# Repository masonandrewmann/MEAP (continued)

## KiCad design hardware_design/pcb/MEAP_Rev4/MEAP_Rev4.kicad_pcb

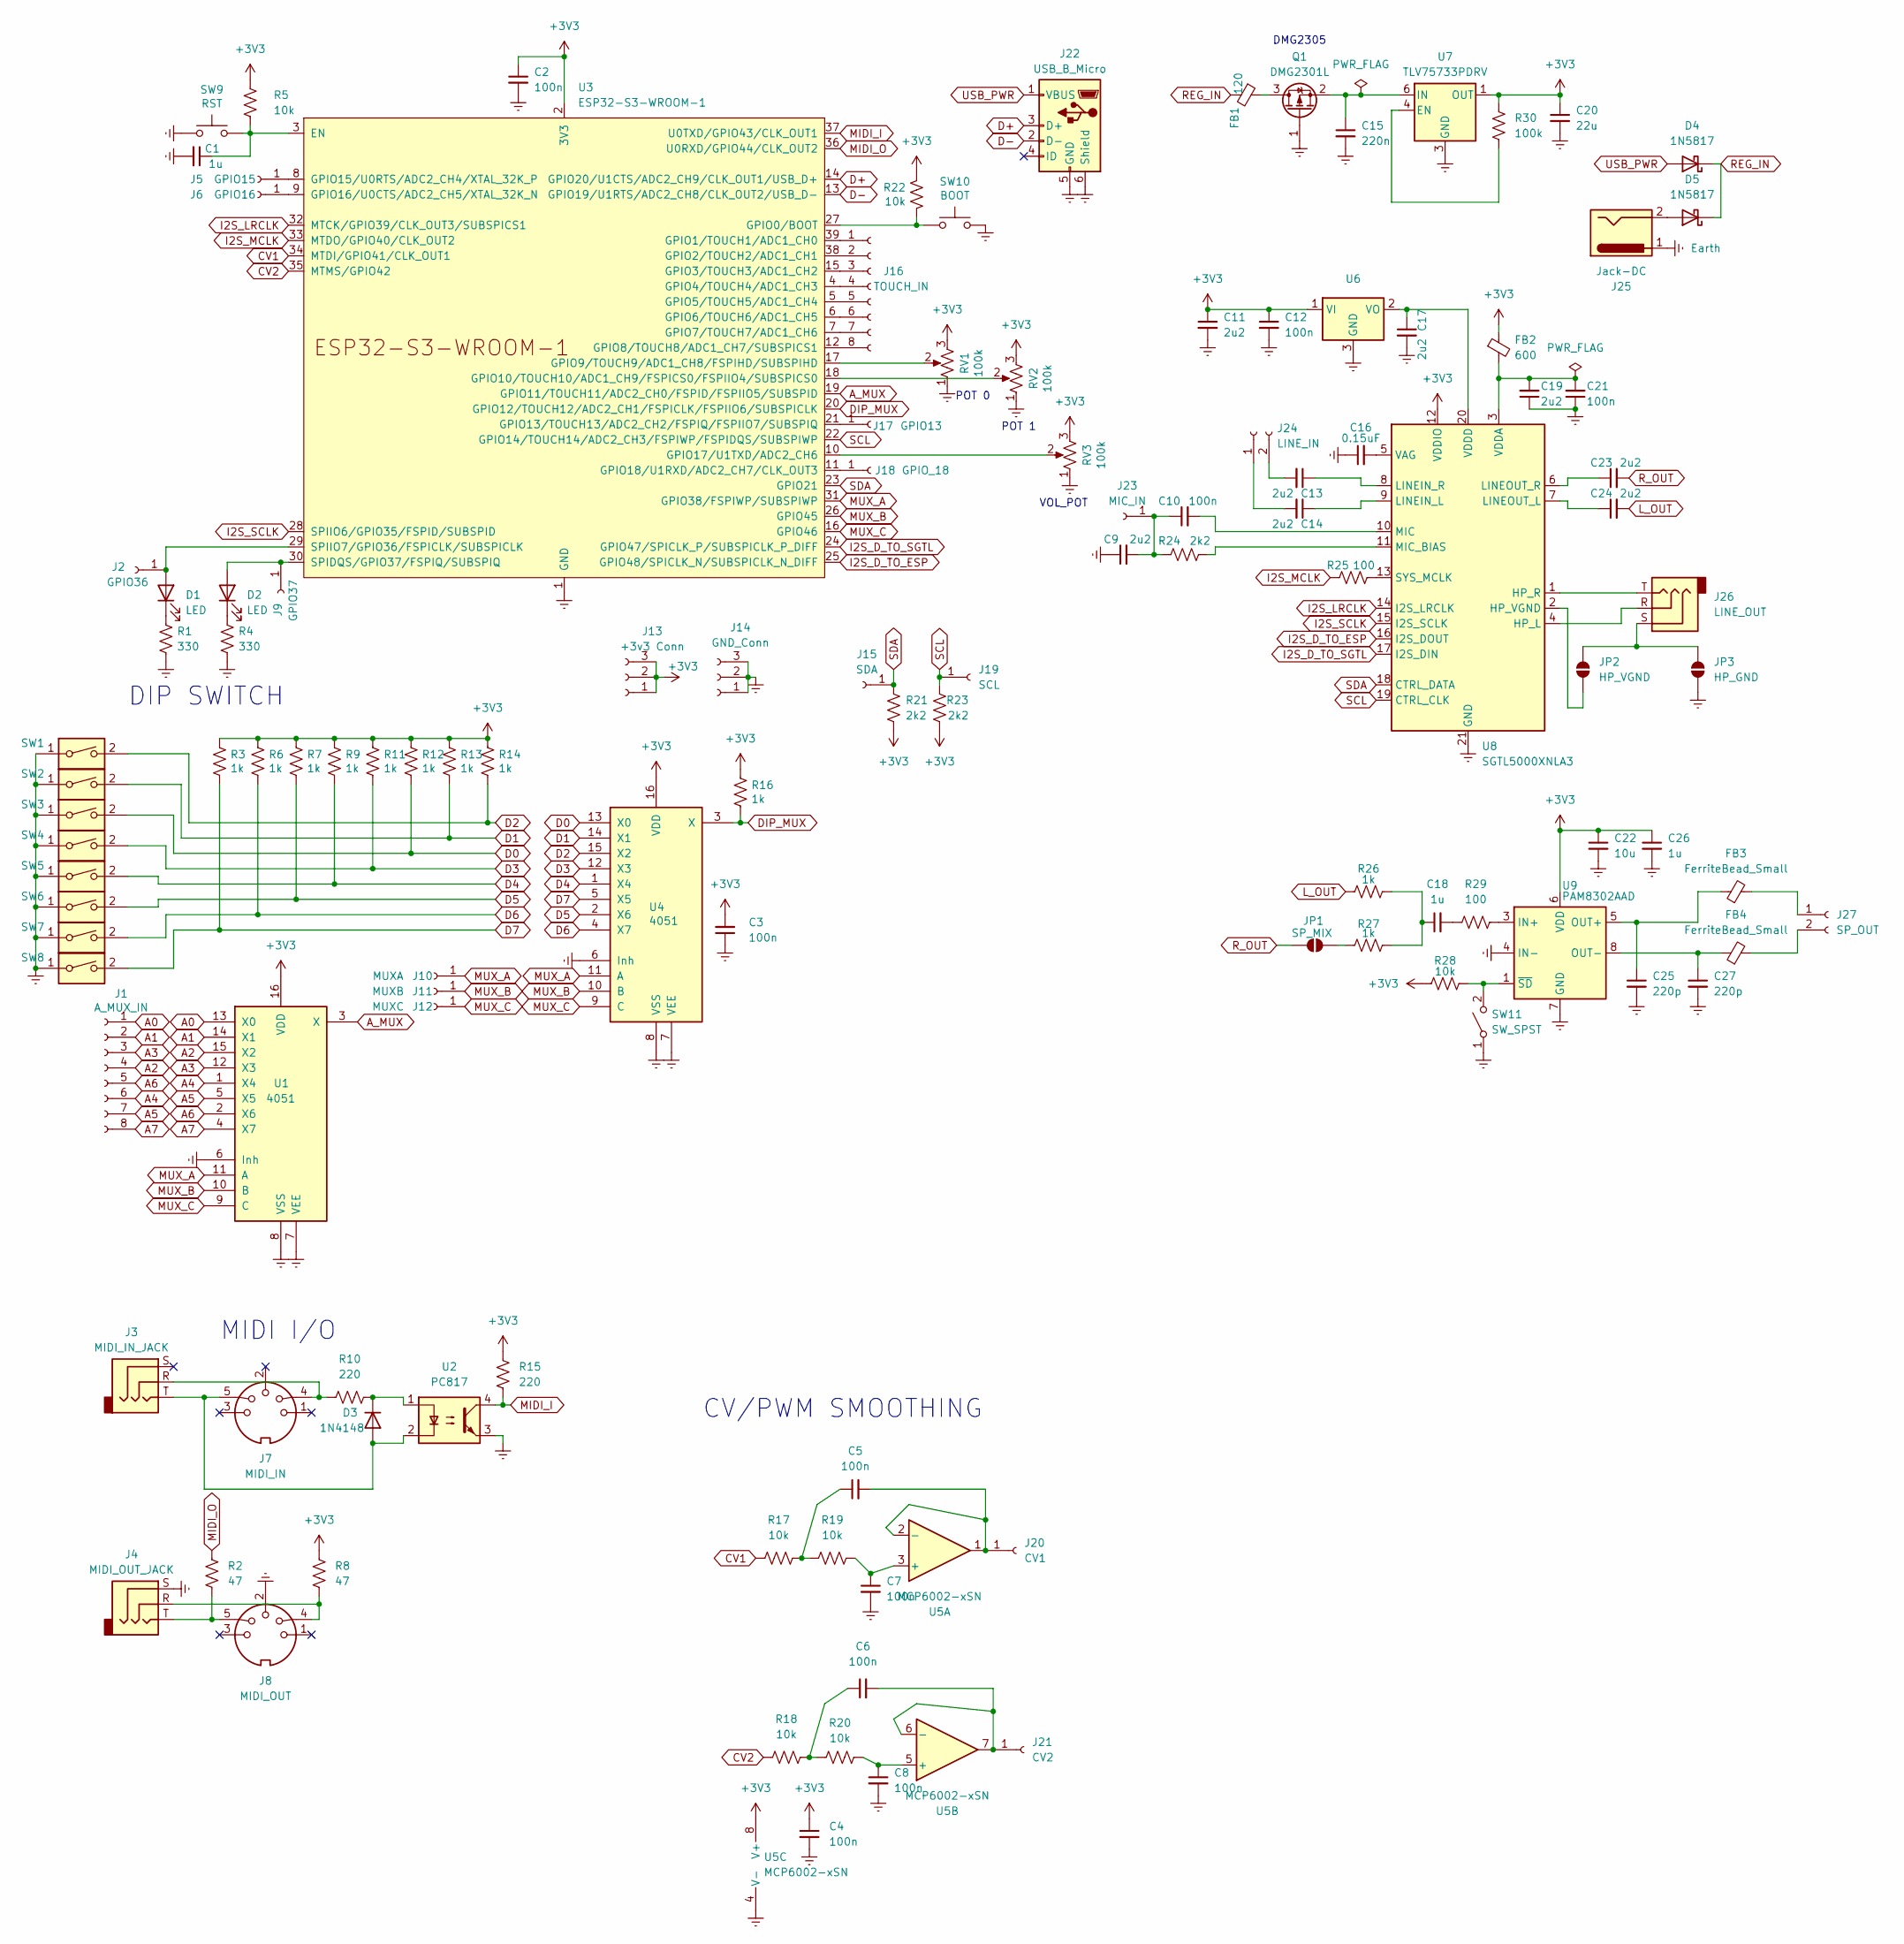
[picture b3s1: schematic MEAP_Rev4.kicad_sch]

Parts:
C1, C18, C26: 1u; C_0603_1608Metric_Pad1.08x0.95mm_HandSolder
C2, C3, C4, C5, C6, C7, C8, C10, C12, C21: 100n; C_0603_1608Metric_Pad1.08x0.95mm_HandSolder
C9, C11, C13, C14, C17, C19, C23, C24: 2u2; C_0603_1608Metric_Pad1.08x0.95mm_HandSolder
C15: 220n; C_0603_1608Metric_Pad1.08x0.95mm_HandSolder
C16: 0.15uF; C_0603_1608Metric_Pad1.08x0.95mm_HandSolder
C20: 22u; C_1210_3225Metric
C22: 10u; C_0603_1608Metric_Pad1.08x0.95mm_HandSolder
C25, C27: 220p; C_0603_1608Metric_Pad1.08x0.95mm_HandSolder
D1, D2: LED; LED_D3.0mm_Clear
D3: 1N4148; D_SOD-323
D4, D5: 1N5817; D_DO-41_SOD81_P2.54mm_Vertical_KathodeUp
FB1: 120; L_0603_1608Metric
FB2: 600; L_0603_1608Metric
FB3, FB4: FerriteBead_Small; L_0603_1608Metric
J1: A_MUX_IN; PinHeader_2x04_P2.54mm_Vertical
J2: GPIO36; Pin_D1.0mm_L10.0mm
J3: MIDI_IN_JACK; Jack_3.5mm_CUI_SJ1-3535NG_Horizontal_NO_FRONT
J4: MIDI_OUT_JACK; Jack_3.5mm_CUI_SJ1-3535NG_Horizontal_NO_FRONT
J5: GPIO15; Pin_D1.0mm_L10.0mm
J6: GPIO16; Pin_D1.0mm_L10.0mm
J7: MIDI_IN
J8: MIDI_OUT
J9: GPIO37; Pin_D1.0mm_L10.0mm
J10: MUXA; Pin_D1.0mm_L10.0mm
J11: MUXB; Pin_D1.0mm_L10.0mm
J12: MUXC; Pin_D1.0mm_L10.0mm
J13: +3v3 Conn; PinHeader_1x03_P2.54mm_Vertical
J14: GND_Conn; PinHeader_1x03_P2.54mm_Vertical
J15: SDA; Pin_D1.0mm_L10.0mm
J16: TOUCH_IN; PinHeader_2x04_P2.54mm_Vertical
J17: GPIO13; Pin_D1.0mm_L10.0mm
J18: GPIO_18; Pin_D1.0mm_L10.0mm
J19: SCL; Pin_D1.0mm_L10.0mm
J20: CV1; Pin_D1.0mm_L10.0mm
J21: CV2; Pin_D1.0mm_L10.0mm
J22: USB_B_Micro; USB_Micro-B_Molex-105017-0001
J23: MIC_IN; Pin_D1.0mm_L10.0mm
J24: LINE_IN; PinHeader_1x02_P2.54mm_Vertical
J25: Jack-DC; BarrelJack_Horizontal
J26: LINE_OUT; Jack_3.5mm_CUI_SJ1-3535NG_Horizontal_NO_FRONT
J27: SP_OUT; PinHeader_1x02_P2.54mm_Vertical
JP1: SP_MIX; SolderJumper-2_P1.3mm_Open_Pad1.0x1.5mm
JP2: HP_VGND; SolderJumper-2_P1.3mm_Open_RoundedPad1.0x1.5mm
JP3: HP_GND; SolderJumper-2_P1.3mm_Open_RoundedPad1.0x1.5mm
Q1: DMG2301L; SOT-23
R1, R4: 330; R_0603_1608Metric_Pad0.98x0.95mm_HandSolder
R2, R8: 47; R_0603_1608Metric_Pad0.98x0.95mm_HandSolder
R3, R6, R7, R9, R11, R12, R13, R14, R16, R26, R27: 1k; R_0603_1608Metric_Pad0.98x0.95mm_HandSolder
R5, R17, R18, R19, R20, R22, R28: 10k; R_0603_1608Metric_Pad0.98x0.95mm_HandSolder
R10, R15: 220; R_0603_1608Metric_Pad0.98x0.95mm_HandSolder
R21, R23, R24: 2k2; R_0603_1608Metric_Pad0.98x0.95mm_HandSolder
R25, R29: 100; R_0603_1608Metric_Pad0.98x0.95mm_HandSolder
R30: 100k; R_0603_1608Metric_Pad0.98x0.95mm_HandSolder
RV1, RV2, RV3: 100k; PinHeader_1x03_P2.54mm_Vertical
SW1, SW2, SW3, SW4, SW5, SW6, SW7, SW8: SW_DIP_x01; SINGLE_DIP_SWITCH
SW9: RST; SW_Tactile_SPST_NO_Straight_CK_PTS636Sx25SMTRLFS
SW10: BOOT; SW_Tactile_SPST_NO_Straight_CK_PTS636Sx25SMTRLFS
SW11: SW_SPST; SW_Slide_SPDT_Straight_CK_OS102011MS2Q
U1, U4: 4051; SOIC-16_3.9x9.9mm_P1.27mm
U2: PC817; DIP-4_W7.62mm
U3: ESP32-S3-WROOM-1; ESP32-S3-WROOM-1U
U5: MCP6002-xSN; SOIC-8_3.9x4.9mm_P1.27mm
U6: SOT-23
U7: TLV75733PDRV; WSON-6-1EP_2x2mm_P0.65mm_EP1x1.6mm
U8: SGTL5000XNLA3; QFN-20-1EP_3x3mm_P0.4mm_EP1.65x1.65mm
U9: PAM8302AAD; MSOP-8_3x3mm_P0.65mm

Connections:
+3V3: C2.1, C3.2, C4.1, C11.1, C12.1, C20.1, C22.1, C26.1, FB2.1, J13.1, J13.2, J13.3, R3.1, R5.1, R6.1, R7.1, R8.1, R9.1, R11.1, R12.1, R13.1, R14.1, R15.1, R16.1, R21.2, R22.1, R23.2, R28.1, R30.1, RV1.3, RV2.3, RV3.3, U1.16 (VDD), U3.2 (3V3), U4.16 (VDD), U5.8 (V+), U6.1 (VI), U7.1 (OUT), U8.12 (VDDIO), U9.6 (VDD)
A0: J1.1, U1.13 (X0)
A1: J1.2, U1.14 (X1)
A2: J1.4, U1.15 (X2)
A3: J1.3, U1.12 (X3)
A4: J1.6, U1.1 (X4)
A5: J1.7, U1.5 (X5)
A6: J1.5, U1.2 (X6)
A7: J1.8, U1.4 (X7)
A_MUX: U1.3 (X), U3.19 (GPIO11/TOUCH11/ADC2_CH0/FSPID/FSPIIO5/S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)
CV1: R17.1, U3.34 (MTDI/GPIO41/CLK_OUT1)
CV2: R18.1, U3.35 (MTMS/GPIO42)
D0: R12.2, SW3.2, U4.13 (X0)
D1: R13.2, SW2.2, U4.14 (X1)
D2: R14.2, SW1.2, U4.15 (X2)
D3: R11.2, SW4.2, U4.12 (X3)
D4: R9.2, SW5.2, U4.1 (X4)
D5: R7.2, SW6.2, U4.2 (X6)
D6: R6.2, SW7.2, U4.4 (X7)
D7: R3.2, SW8.2, U4.5 (X5)
D+: J22.3 (D+), U3.14 (GPIO20/U1CTS/ADC2_CH9/CLK_OUT1/USB_D+)
D-: J22.2 (D-), U3.13 (GPIO19/U1RTS/ADC2_CH8/CLK_OUT2/USB_D-)
DIP_MUX: R16.2, U3.20 (GPIO12/TOUCH12/ADC2_CH1/FSPICLK/FSPIIO6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), U4.3 (X)
Earth: C1.2, C2.2, C3.1, C4.2, C7.2, C8.2, C9.1, C11.2, C12.2, C15.2, C16.1, C17.2, C19.1, C20.2, C21.1, C22.2, C25.2, C26.2, C27.2, J4.S, J8.2, J14.1, J14.2, J14.3, J22.5 (GND), J22.6 (Shield), J25.1, JP3.1 (A), Q1.1 (G), R1.2, R4.2, RV1.1, RV2.1, RV3.1, SW1.1, SW2.1, SW3.1, SW4.1, SW5.1, SW6.1, SW7.1, SW8.1, SW9.1, SW10.2, SW11.1 (A), U1.6 (Inh), U1.7 (VEE), U1.8 (VSS), U2.3, U3.1 (GND), U3.40 (GND), U3.41 (GND), U4.6 (Inh), U4.7 (VEE), U4.8 (VSS), U5.4 (V-), U6.3 (GND), U7.3 (GND), U7.7 (GND), U8.21 (GND), U9.4 (IN-), U9.7 (GND)
I2S_D_TO_ESP: U3.25 (GPIO48/SPICLK_N/SUBSPICLK_N_DIFF), U8.16 (I2S_DOUT)
I2S_D_TO_SGTL: U3.24 (GPIO47/SPICLK_P/SUBSPICLK_P_DIFF), U8.17 (I2S_DIN)
I2S_LRCLK: U3.32 (MTCK/GPIO39/CLK_OUT3/SUBSPICS1), U8.14 (I2S_LRCLK)
I2S_MCLK: R25.1, U3.33 (MTDO/GPIO40/CLK_OUT2)
I2S_SCLK: U3.28 (SPIIO6/GPIO35/FSPID/SUBSPID), U8.15 (I2S_SCLK)
L_OUT: C24.2, R26.1
MIDI_I: R15.2, U2.4, U3.37 (U0TXD/GPIO43/CLK_OUT1)
MIDI_O: R2.1, U3.36 (U0RXD/GPIO44/CLK_OUT2)
MUX_A: J10.1, U1.11 (A), U3.31 (GPIO38/FSPIWP/SUBSPIWP), U4.11 (A)
MUX_B: J11.1, U1.10 (B), U3.26 (GPIO45), U4.10 (B)
MUX_C: J12.1, U1.9 (C), U3.16 (GPIO46), U4.9 (C)
unnamed: C5.1, R17.2, R19.1
unnamed: C6.1, R18.2, R20.1
unnamed: C18.1, R26.2, R27.2
unnamed: C18.2, R29.1
unnamed: D1.2 (A), J2.1, U3.29 (SPIIO7/GPIO36/FSPICLK/SUBSPICLK)
unnamed: D1.1 (K), R1.1
unnamed: D2.2 (A), J9.1, U3.30 (SPIDQS/GPIO37/FSPIQ/SUBSPIQ)
unnamed: D2.1 (K), R4.1
unnamed: D3.2 (A), J3.T, J7.5, U2.2
unnamed: D3.1 (K), R10.2, U2.1
unnamed: D5.2 (A), J25.2
unnamed: J3.R, J7.4, R10.1
unnamed: J4.R, J8.4, R8.2
unnamed: J4.T, J8.5, R2.2
unnamed: J5.1, U3.8 (GPIO15/U0RTS/ADC2_CH4/XTAL_32K_P)
unnamed: J6.1, U3.9 (GPIO16/U0CTS/ADC2_CH5/XTAL_32K_N)
unnamed: J16.1, U3.39 (GPIO1/TOUCH1/ADC1_CH0)
unnamed: J16.2, U3.38 (GPIO2/TOUCH2/ADC1_CH1)
unnamed: J16.3, U3.15 (GPIO3/TOUCH3/ADC1_CH2)
unnamed: J16.4, U3.4 (GPIO4/TOUCH4/ADC1_CH3)
unnamed: J16.5, U3.5 (GPIO5/TOUCH5/ADC1_CH4)
unnamed: J16.6, U3.6 (GPIO6/TOUCH6/ADC1_CH5)
unnamed: J16.7, U3.7 (GPIO7/TOUCH7/ADC1_CH6)
unnamed: J16.8, U3.12 (GPIO8/TOUCH8/ADC1_CH7/SUBSPICS1)
unnamed: J17.1, U3.21 (GPIO13/TOUCH13/ADC2_CH2/FSPIQ/FSPIIO7/S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)
unnamed: J18.1, U3.11 (GPIO18/U1RXD/ADC2_CH7/CLK_OUT3)
unnamed: C5.2, J20.1, U5.1, U5.2 (-)
unnamed: C6.2, J21.1, U5.6 (-), U5.7
unnamed: C9.2, C10.1, J23.1, R24.1
unnamed: C14.2, J24.1
unnamed: C13.2, J24.2
unnamed: FB3.2, J27.1
unnamed: FB4.2, J27.2
unnamed: JP1.1 (A), R27.1
unnamed: JP2.1 (A), U8.2 (HP_VGND)
unnamed: J26.S, JP2.2 (B), JP3.2 (B)
unnamed: FB1.1, Q1.3 (D)
unnamed: C15.1, Q1.2 (S), U7.6 (IN)
unnamed: R28.2, SW11.2 (B), U9.1 (~SD)
unnamed: C1.1, R5.2, SW9.2, U3.3 (EN)
unnamed: R22.2, SW10.1, U3.27 (GPIO0/BOOT)
unnamed: RV1.2, U3.17 (GPIO9/TOUCH9/ADC1_CH8/FSPIHD/SUBSPIHD)
unnamed: RV2.2, U3.18 (GPIO10/TOUCH10/ADC1_CH9/FSPICS0/FSPIIO4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)
unnamed: RV3.2, U3.10 (GPIO17/U1TXD/ADC2_CH6)
unnamed: C7.1, R19.2, U5.3 (+)
unnamed: C8.1, R20.2, U5.5 (+)
unnamed: C17.1, U6.2 (VO), U8.20 (VDDD)
unnamed: R30.2, U7.4 (EN)
unnamed: J26.R, U8.4 (HP_L)
unnamed: J26.T, U8.1 (HP_R)
unnamed: C14.1, U8.9 (LINEIN_L)
unnamed: C13.1, U8.8 (LINEIN_R)
unnamed: C24.1, U8.7 (LINEOUT_L)
unnamed: C23.1, U8.6 (LINEOUT_R)
unnamed: C10.2, U8.10 (MIC)
unnamed: R24.2, U8.11 (MIC_BIAS)
unnamed: R25.2, U8.13 (SYS_MCLK)
unnamed: C16.2, U8.5 (VAG)
unnamed: C19.2, C21.2, FB2.2, U8.3 (VDDA)
unnamed: R29.2, U9.3 (IN+)
unnamed: C25.1, FB3.1, U9.5 (OUT+)
unnamed: C27.1, FB4.1, U9.8 (OUT-)
REG_IN: D4.1 (K), D5.1 (K), FB1.2
R_OUT: C23.2, JP1.2 (B)
SCL: J19.1, R23.1, U3.22 (GPIO14/TOUCH14/ADC2_CH3/FSPIWP/FSPIDQS/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), U8.19 (CTRL_CLK)
SDA: J15.1, R21.1, U3.23 (GPIO21), U8.18 (CTRL_DATA)
USB_PWR: D4.2 (A), J22.1 (VBUS)

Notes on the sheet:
CV/PWM SMOOTHING
VOL_POT
POT 1
DMG2305
POT 0
DIP SWITCH
MIDI I/O

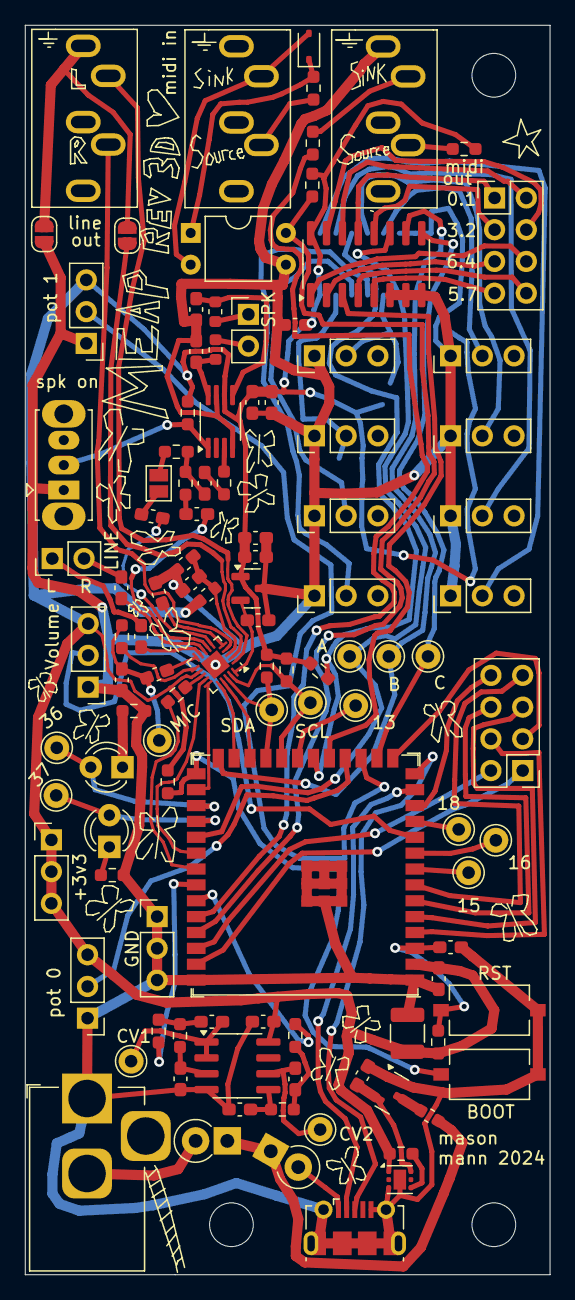
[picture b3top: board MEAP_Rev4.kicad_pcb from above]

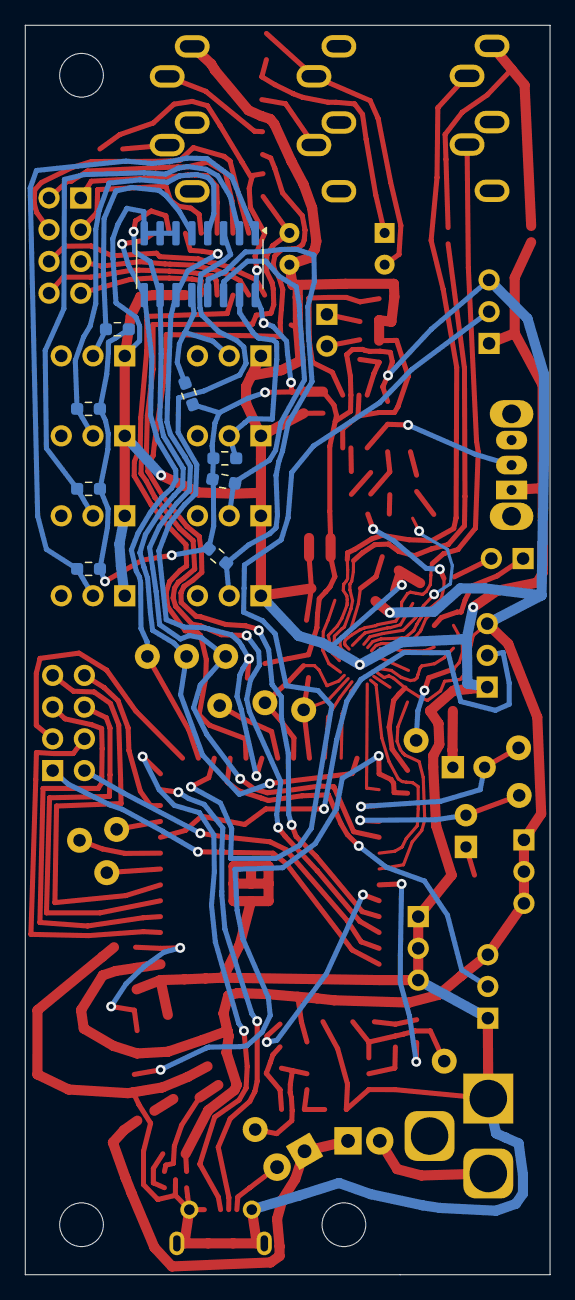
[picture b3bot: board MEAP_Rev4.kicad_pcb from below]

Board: 2 copper layers, 42.0 x 100.0 mm, 118 parts (9 on the bottom side), 102 nets.

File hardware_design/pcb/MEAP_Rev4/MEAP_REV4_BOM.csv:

"Reference","Value","Footprint","Qty","DNP"
"U9","PAM8302AAD","Package_SO:MSOP-8_3x3mm_P0.65mm","1",""
"U8","SGTL5000XNLA3","Package_DFN_QFN:QFN-20-1EP_3x3mm_P0.4mm_EP1.65x1.65mm","1",""
"U7","TLV75733PDRV","Package_SON:WSON-6-1EP_2x2mm_P0.65mm_EP1x1.6mm","1",""
"U6","~","Package_TO_SOT_SMD:SOT-23","1",""
"U5","MCP6002-xSN","Package_SO:SOIC-8_3.9x4.9mm_P1.27mm","1",""
"U3","ESP32-S3-WROOM-1","PCM_Espressif:ESP32-S3-WROOM-1U","1",""
"U2","PC817","Package_DIP:DIP-4_W7.62mm","1",""
"U1,U4","4051","Package_SO:SOIC-16_3.9x9.9mm_P1.27mm","2",""
"SW11","SW_SPST","Button_Switch_THT:SW_Slide_SPDT_Straight_CK_OS102011MS2Q","1",""
"SW10","BOOT","Button_Switch_SMD:SW_Tactile_SPST_NO_Straight_CK_PTS636Sx25SMTRLFS","1",""
"SW9","RST","Button_Switch_SMD:SW_Tactile_SPST_NO_Straight_CK_PTS636Sx25SMTRLFS","1",""
"SW1,SW2,SW3,SW4,SW5,SW6,SW7,SW8","SW_DIP_x01","mason_parts:SINGLE_DIP_SWITCH","8",""
"RV1,RV2,RV3","100k","Connector_PinHeader_2.54mm:PinHeader_1x03_P2.54mm_Vertical","3",""
"R30","100k","Resistor_SMD:R_0603_1608Metric_Pad0.98x0.95mm_HandSolder","1",""
"R25,R29","100","Resistor_SMD:R_0603_1608Metric_Pad0.98x0.95mm_HandSolder","2",""
"R21,R23,R24","2k2","Resistor_SMD:R_0603_1608Metric_Pad0.98x0.95mm_HandSolder","3",""
"R10,R15","220","Resistor_SMD:R_0603_1608Metric_Pad0.98x0.95mm_HandSolder","2",""
"R5,R17,R18,R19,R20,R22,R28","10k","Resistor_SMD:R_0603_1608Metric_Pad0.98x0.95mm_HandSolder","7",""
"R3,R6,R7,R9,R11,R12,R13,R14,R16,R26,R27","1k","Resistor_SMD:R_0603_1608Metric_Pad0.98x0.95mm_HandSolder","11",""
"R2,R8","47","Resistor_SMD:R_0603_1608Metric_Pad0.98x0.95mm_HandSolder","2",""
"R1,R4","330","Resistor_SMD:R_0603_1608Metric_Pad0.98x0.95mm_HandSolder","2",""
"Q1","DMG2301L","Package_TO_SOT_SMD:SOT-23","1",""
"J27","SP_OUT","Connector_PinHeader_2.54mm:PinHeader_1x02_P2.54mm_Vertical","1",""
"J26","LINE_OUT","mason_parts:Jack_3.5mm_CUI_SJ1-3535NG_Horizontal_NO_FRONT","1",""
"J25","Jack-DC","mason_parts:BarrelJack_Horizontal","1",""
"J24","LINE_IN","Connector_PinHeader_2.54mm:PinHeader_1x02_P2.54mm_Vertical","1",""
"J23","MIC_IN","Connector_Pin:Pin_D1.0mm_L10.0mm","1",""
"J22","USB_B_Micro","Connector_USB:USB_Micro-B_Molex-105017-0001","1",""
"J21","CV2","Connector_Pin:Pin_D1.0mm_L10.0mm","1",""
"J20","CV1","Connector_Pin:Pin_D1.0mm_L10.0mm","1",""
"J19","SCL","Connector_Pin:Pin_D1.0mm_L10.0mm","1",""
"J18","GPIO_18","Connector_Pin:Pin_D1.0mm_L10.0mm","1",""
"J17","GPIO13","Connector_Pin:Pin_D1.0mm_L10.0mm","1",""
"J16","TOUCH_IN","Connector_PinHeader_2.54mm:PinHeader_2x04_P2.54mm_Vertical","1",""
"J15","SDA","Connector_Pin:Pin_D1.0mm_L10.0mm","1",""
"J14","GND_Conn","Connector_PinHeader_2.54mm:PinHeader_1x03_P2.54mm_Vertical","1",""
"J13","+3v3 Conn","Connector_PinHeader_2.54mm:PinHeader_1x03_P2.54mm_Vertical","1",""
"J12","MUXC","Connector_Pin:Pin_D1.0mm_L10.0mm","1",""
"J11","MUXB","Connector_Pin:Pin_D1.0mm_L10.0mm","1",""
"J10","MUXA","Connector_Pin:Pin_D1.0mm_L10.0mm","1",""
"J9","GPIO37","Connector_Pin:Pin_D1.0mm_L10.0mm","1",""
"J8","MIDI_OUT","","1",""
"J7","MIDI_IN","","1",""
"J6","GPIO16","Connector_Pin:Pin_D1.0mm_L10.0mm","1",""
"J5","GPIO15","Connector_Pin:Pin_D1.0mm_L10.0mm","1",""
"J4","MIDI_OUT_JACK","mason_parts:Jack_3.5mm_CUI_SJ1-3535NG_Horizontal_NO_FRONT","1",""
"J3","MIDI_IN_JACK","mason_parts:Jack_3.5mm_CUI_SJ1-3535NG_Horizontal_NO_FRONT","1",""
"J2","GPIO36","Connector_Pin:Pin_D1.0mm_L10.0mm","1",""
"J1","A_MUX_IN","Connector_PinHeader_2.54mm:PinHeader_2x04_P2.54mm_Vertical","1",""
"FB3,FB4","FerriteBead_Small","Inductor_SMD:L_0603_1608Metric","2",""
"FB2","600","Inductor_SMD:L_0603_1608Metric","1",""
"FB1","120","Inductor_SMD:L_0603_1608Metric","1",""
"D4,D5","1N5817","Diode_THT:D_DO-41_SOD81_P2.54mm_Vertical_KathodeUp","2",""
"D3","1N4148","Diode_SMD:D_SOD-323","1",""
"D1,D2","LED","LED_THT:LED_D3.0mm_Clear","2",""
"C25,C27","220p","Capacitor_SMD:C_0603_1608Metric_Pad1.08x0.95mm_HandSolder","2",""
"C22","10u","Capacitor_SMD:C_0603_1608Metric_Pad1.08x0.95mm_HandSolder","1",""
"C20","22u","Capacitor_SMD:C_1210_3225Metric","1",""
"C16","0.15uF","Capacitor_SMD:C_0603_1608Metric_Pad1.08x0.95mm_HandSolder","1",""
"C15","220n","Capacitor_SMD:C_0603_1608Metric_Pad1.08x0.95mm_HandSolder","1",""
"C9,C11,C13,C14,C17,C19,C23,C24","2u2","Capacitor_SMD:C_0603_1608Metric_Pad1.08x0.95mm_HandSolder","8",""
"C2,C3,C4,C5,C6,C7,C8,C10,C12,C21","100n","Capacitor_SMD:C_0603_1608Metric_Pad1.08x0.95mm_HandSolder","10",""
"C1,C18,C26","1u","Capacitor_SMD:C_0603_1608Metric_Pad1.08x0.95mm_HandSolder","3",""

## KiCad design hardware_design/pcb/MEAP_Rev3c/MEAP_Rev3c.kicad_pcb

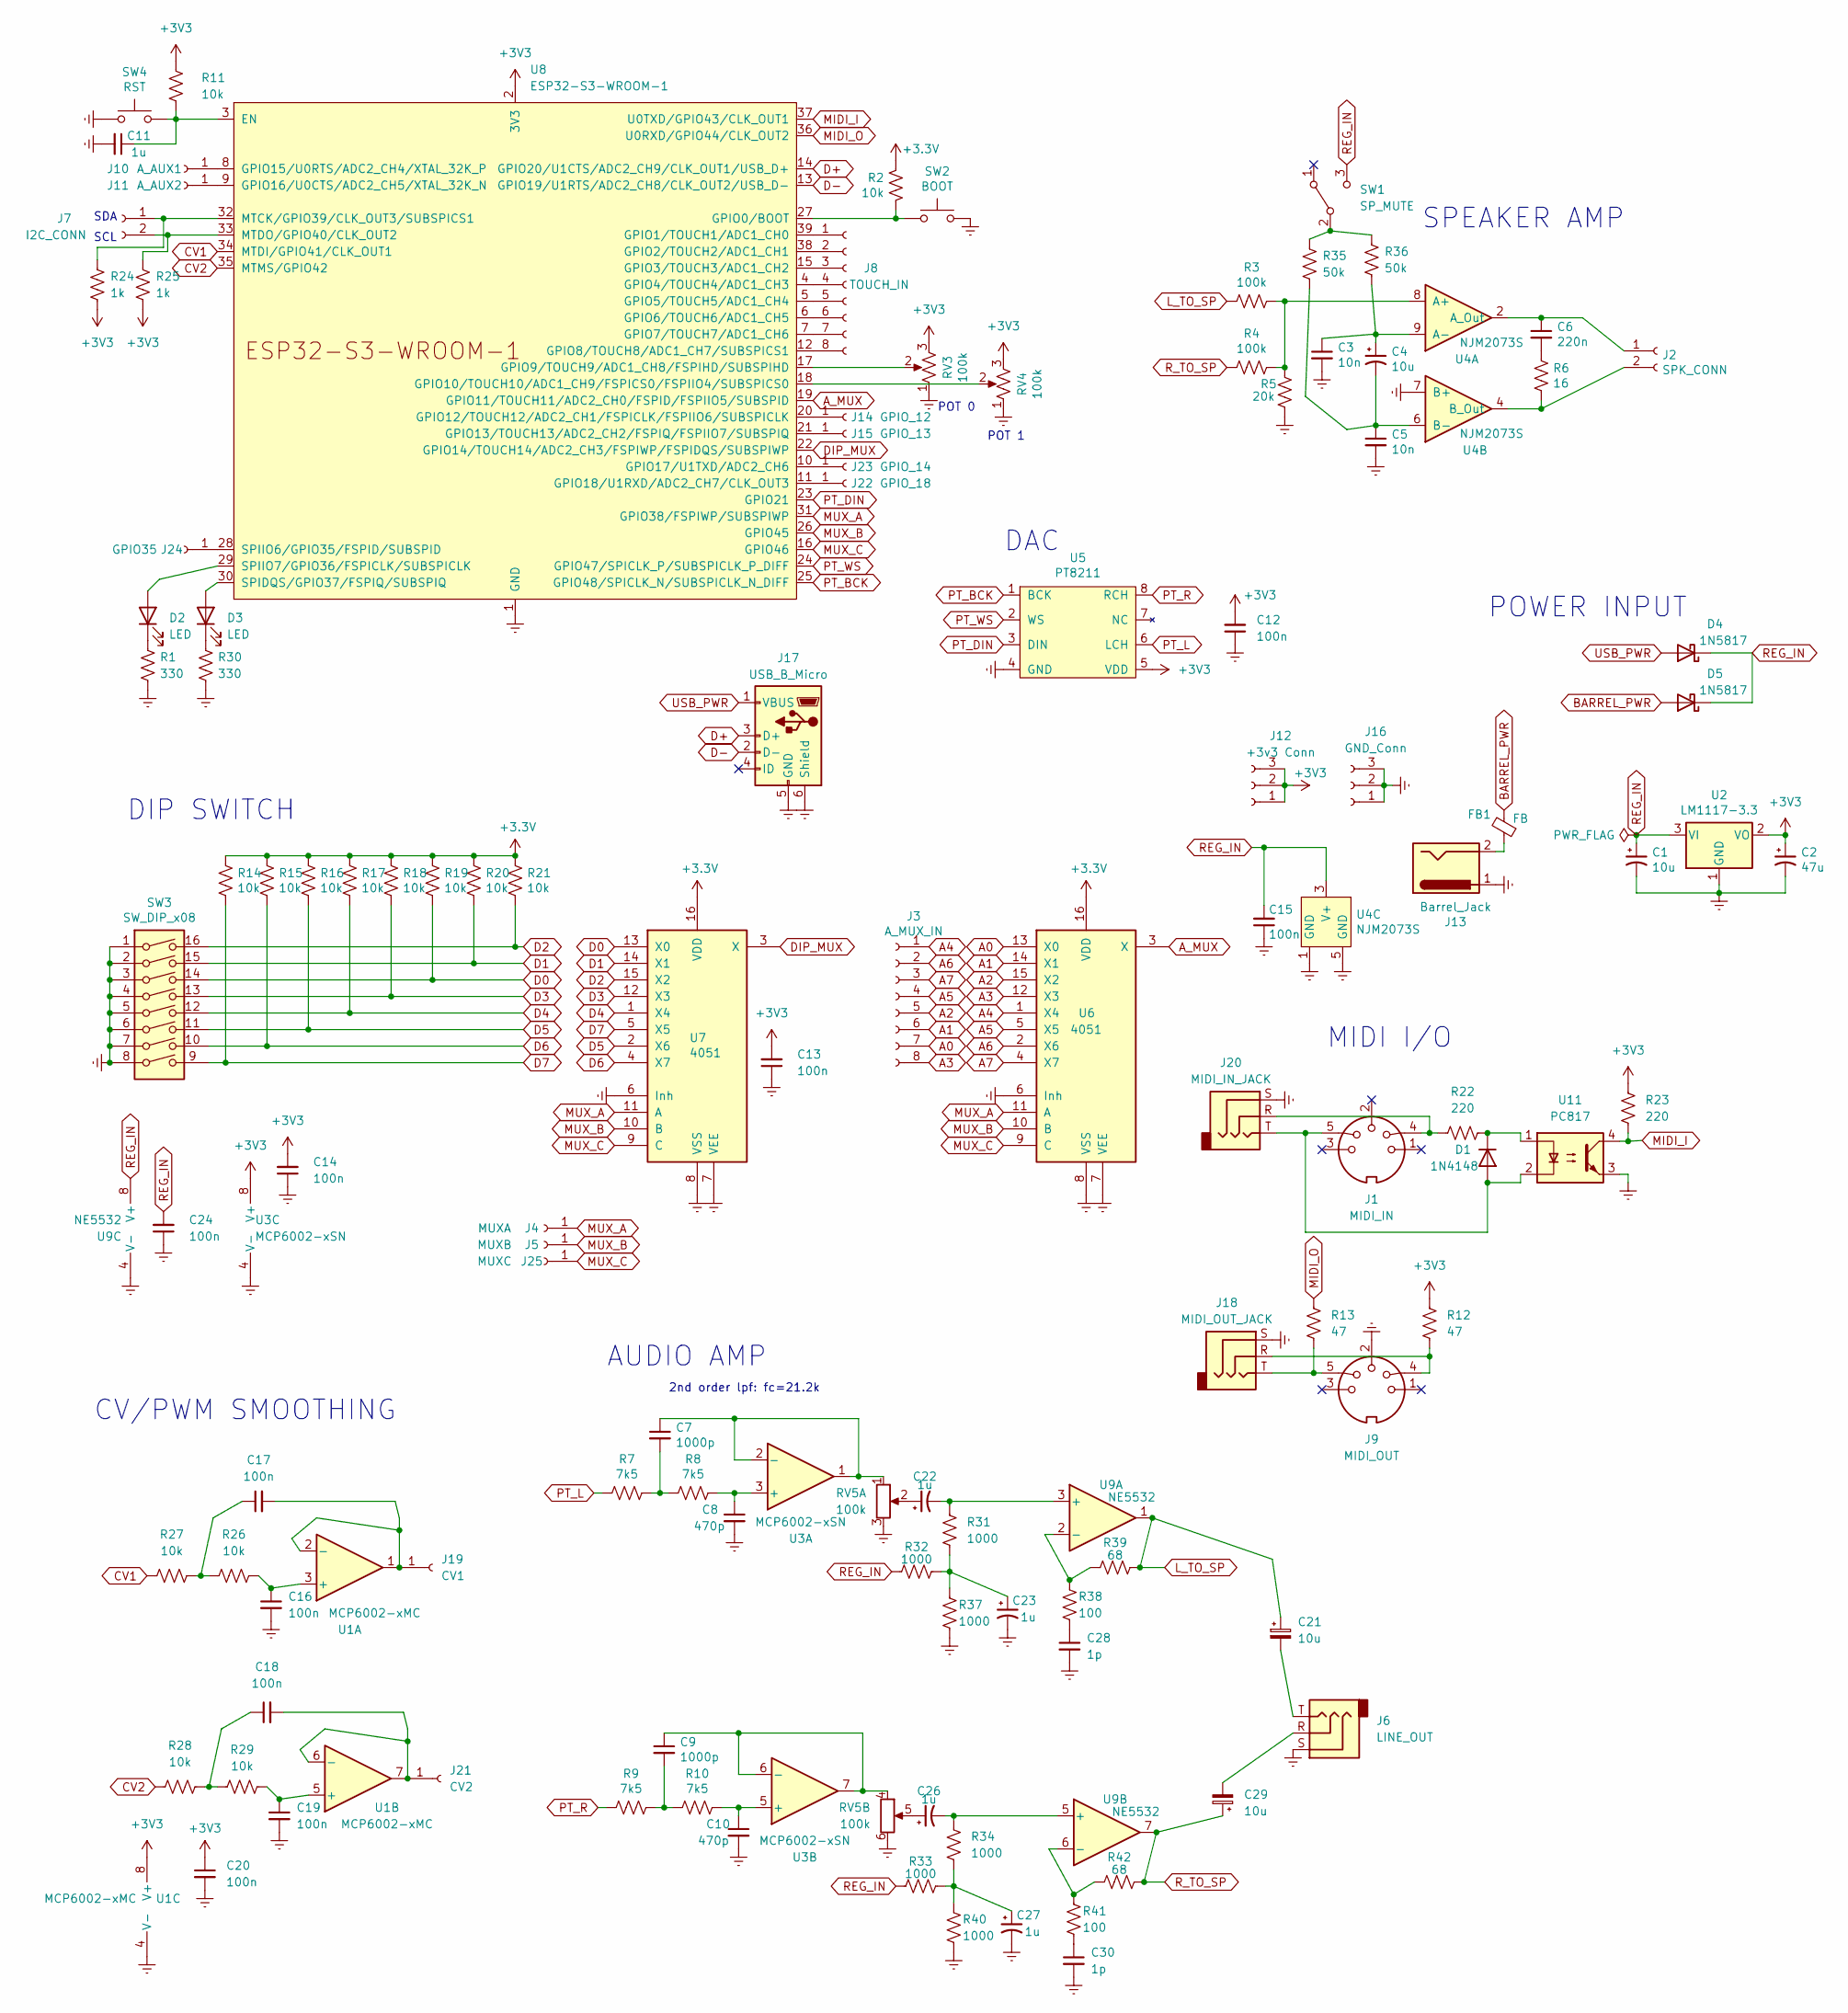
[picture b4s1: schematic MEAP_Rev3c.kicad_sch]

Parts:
C1, C4, C21, C29: 10u; C_0805_2012Metric_Pad1.18x1.45mm_HandSolder
C2: 47u; C_0805_2012Metric_Pad1.18x1.45mm_HandSolder
C3, C5: 10n; C_0603_1608Metric_Pad1.08x0.95mm_HandSolder
C6: 220n; C_0603_1608Metric_Pad1.08x0.95mm_HandSolder
C7, C9: 1000p; C_0603_1608Metric_Pad1.08x0.95mm_HandSolder
C8, C10: 470p; C_0603_1608Metric_Pad1.08x0.95mm_HandSolder
C11, C22, C23, C26, C27: 1u; C_0805_2012Metric_Pad1.18x1.45mm_HandSolder
C12, C13, C14, C15, C16, C17, C18, C19, C20, C24: 100n; C_0603_1608Metric_Pad1.08x0.95mm_HandSolder
C28, C30: 1p; C_0603_1608Metric_Pad1.08x0.95mm_HandSolder
D1: 1N4148; D_SOD-323
D2, D3: LED; LED_D3.0mm_Clear
D4, D5: 1N5817; D_DO-41_SOD81_P2.54mm_Vertical_AnodeUp
FB1: FB; L_0805_2012Metric_Pad1.15x1.40mm_HandSolder
J1: MIDI_IN
J2: SPK_CONN; PinHeader_1x02_P2.54mm_Vertical
J3: A_MUX_IN; PinHeader_2x04_P2.54mm_Vertical
J4: MUXA; Pin_D1.0mm_L10.0mm
J5: MUXB; Pin_D1.0mm_L10.0mm
J6: LINE_OUT; Jack_3.5mm_CUI_SJ1-3535NG_Horizontal_NO_FRONT
J7: I2C_CONN; PinHeader_1x02_P2.54mm_Vertical
J8: TOUCH_IN; PinHeader_2x04_P2.54mm_Vertical
J9: MIDI_OUT
J10: A_AUX1; Pin_D1.0mm_L10.0mm
J11: A_AUX2; Pin_D1.0mm_L10.0mm
J12: +3v3 Conn; PinHeader_1x03_P2.54mm_Vertical
J13: Barrel_Jack; BarrelJack_Horizontal
J14: GPIO_12; Pin_D1.0mm_L10.0mm
J15: GPIO_13; Pin_D1.0mm_L10.0mm
J16: GND_Conn; PinHeader_1x03_P2.54mm_Vertical
J17: USB_B_Micro; USB_Micro-B_Molex-105017-0001
J18: MIDI_OUT_JACK; Jack_3.5mm_CUI_SJ1-3535NG_Horizontal_NO_FRONT
J19: CV1; Pin_D1.0mm_L10.0mm
J20: MIDI_IN_JACK; Jack_3.5mm_CUI_SJ1-3535NG_Horizontal_NO_FRONT
J21: CV2; Pin_D1.0mm_L10.0mm
J22: GPIO_18; Pin_D1.0mm_L10.0mm
J23: GPIO_14; Pin_D1.0mm_L10.0mm
J24: GPIO35; Pin_D1.0mm_L10.0mm
J25: MUXC; Pin_D1.0mm_L10.0mm
R1, R30: 330; R_0603_1608Metric_Pad0.98x0.95mm_HandSolder
R2, R11, R14, R15, R16, R17, R18, R19, R20, R21, R26, R27, R28, R29: 10k; R_0603_1608Metric_Pad0.98x0.95mm_HandSolder
R3, R4: 100k; R_0603_1608Metric_Pad0.98x0.95mm_HandSolder
R5: 20k; R_0603_1608Metric_Pad0.98x0.95mm_HandSolder
R6: 16; R_0603_1608Metric_Pad0.98x0.95mm_HandSolder
R7, R8, R9, R10: 7k5; R_0603_1608Metric_Pad0.98x0.95mm_HandSolder
R12, R13: 47; R_0603_1608Metric_Pad0.98x0.95mm_HandSolder
R22, R23: 220; R_0603_1608Metric_Pad0.98x0.95mm_HandSolder
R24, R25: 1k; R_0603_1608Metric_Pad0.98x0.95mm_HandSolder
R31, R32, R33, R34, R37, R40: 1000; R_0603_1608Metric_Pad0.98x0.95mm_HandSolder
R35, R36: 50k; R_0603_1608Metric_Pad0.98x0.95mm_HandSolder
R38, R41: 100; R_0603_1608Metric_Pad0.98x0.95mm_HandSolder
R39, R42: 68; R_0603_1608Metric_Pad0.98x0.95mm_HandSolder
RV3, RV4: 100k; PinHeader_1x03_P2.54mm_Vertical
RV5: 100k; Dual_Green_Pot
SW1: SP_MUTE; PinHeader_1x03_P2.54mm_Vertical
SW2: BOOT; SW_Tactile_SPST_NO_Straight_CK_PTS636Sx25SMTRLFS
SW3: SW_DIP_x08; DIP-16_W7.62mm_Socket
SW4: RST; SW_Tactile_SPST_NO_Straight_CK_PTS636Sx25SMTRLFS
U1: MCP6002-xMC; SOIC-8_3.9x4.9mm_P1.27mm
U2: LM1117-3.3; SOT-223
U3: MCP6002-xSN; SOIC-8_3.9x4.9mm_P1.27mm
U4: NJM2073S; SIP-9_21.54x3mm_P2.54mm
U5: PT8211; SOIC-8_3.9x4.9mm_P1.27mm
U6, U7: 4051; SOIC-16_3.9x9.9mm_P1.27mm
U8: ESP32-S3-WROOM-1
U9: NE5532; SOIC-8_3.9x4.9mm_P1.27mm
U11: PC817; DIP-4_W7.62mm

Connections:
A0: J3.7, U6.13 (X0)
A1: J3.6, U6.14 (X1)
A2: J3.5, U6.15 (X2)
A3: J3.8, U6.12 (X3)
A4: J3.1, U6.1 (X4)
A5: J3.4, U6.5 (X5)
A6: J3.2, U6.2 (X6)
A7: J3.3, U6.4 (X7)
A_MUX: U6.3 (X), U8.19 (GPIO11/TOUCH11/ADC2_CH0/FSPID/FSPIIO5/S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)
BARREL_PWR: D5.2 (A), FB1.2
CV1: R27.1, U8.34 (MTDI/GPIO41/CLK_OUT1)
CV2: R28.1, U8.35 (MTMS/GPIO42)
D0: R19.2, SW3.14, U7.13 (X0)
D1: R20.2, SW3.15, U7.14 (X1)
D2: R21.2, SW3.16, U7.15 (X2)
D3: R18.2, SW3.13, U7.12 (X3)
D4: R17.2, SW3.12, U7.1 (X4)
D5: R16.2, SW3.11, U7.2 (X6)
D6: R15.2, SW3.10, U7.4 (X7)
D7: R14.2, SW3.9, U7.5 (X5)
D+: J17.3 (D+), U8.14 (GPIO20/U1CTS/ADC2_CH9/CLK_OUT1/USB_D+)
D-: J17.2 (D-), U8.13 (GPIO19/U1RTS/ADC2_CH8/CLK_OUT2/USB_D-)
DIP_MUX: U7.3 (X), U8.22 (GPIO14/TOUCH14/ADC2_CH3/FSPIWP/FSPIDQS/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)
Earth: C1.2, C2.2, C3.2, C5.2, C8.2, C10.2, C11.2, C12.1, C13.1, C14.1, C15.1, C16.2, C19.2, C20.2, C23.2, C24.1, C27.2, C28.2, C30.2, J6.S, J9.2, J13.1, J16.1, J16.2, J16.3, J17.5 (GND), J17.6 (Shield), J18.S, J20.S, R1.2, R5.1, R30.2, R37.2, R40.2, RV3.1, RV4.1, RV5.3, RV5.6, SW2.2, SW3.1, SW3.2, SW3.3, SW3.4, SW3.5, SW3.6, SW3.7, SW3.8, SW4.1, U1.4 (V-), U1.9 (V-), U2.1 (GND), U3.4 (V-), U4.1 (GND), U4.5 (GND), U4.7 (B+), U5.4 (GND), U6.6 (Inh), U6.7 (VEE), U6.8 (VSS), U7.6 (Inh), U7.7 (VEE), U7.8 (VSS), U8.1 (GND), U8.40 (GND), U8.41 (GND), U9.4 (V-), U11.3
L_TO_SP: C21.1, R3.2, R39.1, U9.1
MIDI_I: R23.2, U8.37 (U0TXD/GPIO43/CLK_OUT1), U11.4
MIDI_O: R13.1, U8.36 (U0RXD/GPIO44/CLK_OUT2)
MUX_A: J4.1, U6.11 (A), U7.11 (A), U8.31 (GPIO38/FSPIWP/SUBSPIWP)
MUX_B: J5.1, U6.10 (B), U7.10 (B), U8.26 (GPIO45)
MUX_C: J25.1, U6.9 (C), U7.9 (C), U8.16 (GPIO46)
unnamed: C6.2, R6.1
unnamed: C7.2, R7.2, R8.1
unnamed: C9.2, R9.2, R10.1
unnamed: C17.1, R26.1, R27.2
unnamed: C18.1, R28.2, R29.1
unnamed: C21.2, J6.T
unnamed: C22.1, RV5.2
unnamed: C23.1, R31.2, R32.2, R37.1
unnamed: C26.1, RV5.5
unnamed: C27.1, R33.2, R34.2, R40.1
unnamed: C28.1, R38.2
unnamed: C29.2, J6.R
unnamed: C30.1, R41.2
unnamed: D1.2 (A), J1.5, J20.T, U11.2
unnamed: D1.1 (K), R22.2, U11.1
unnamed: D2.2 (A), U8.29 (SPIIO7/GPIO36/FSPICLK/SUBSPICLK)
unnamed: D2.1 (K), R1.1
unnamed: D3.2 (A), U8.30 (SPIDQS/GPIO37/FSPIQ/SUBSPIQ)
unnamed: D3.1 (K), R30.1
unnamed: FB1.1, J13.2
unnamed: J1.4, J20.R, R22.1
unnamed: C6.1, J2.1, U4.2 (A_Out)
unnamed: J2.2, R6.2, U4.4 (B_Out)
unnamed: J7.1, R24.1, U8.32 (MTCK/GPIO39/CLK_OUT3/SUBSPICS1)
unnamed: J7.2, R25.1, U8.33 (MTDO/GPIO40/CLK_OUT2)
unnamed: J8.1, U8.39 (GPIO1/TOUCH1/ADC1_CH0)
unnamed: J8.2, U8.38 (GPIO2/TOUCH2/ADC1_CH1)
unnamed: J8.3, U8.15 (GPIO3/TOUCH3/ADC1_CH2)
unnamed: J8.4, U8.4 (GPIO4/TOUCH4/ADC1_CH3)
unnamed: J8.5, U8.5 (GPIO5/TOUCH5/ADC1_CH4)
unnamed: J8.6, U8.6 (GPIO6/TOUCH6/ADC1_CH5)
unnamed: J8.7, U8.7 (GPIO7/TOUCH7/ADC1_CH6)
unnamed: J8.8, U8.12 (GPIO8/TOUCH8/ADC1_CH7/SUBSPICS1)
unnamed: J10.1, U8.8 (GPIO15/U0RTS/ADC2_CH4/XTAL_32K_P)
unnamed: J11.1, U8.9 (GPIO16/U0CTS/ADC2_CH5/XTAL_32K_N)
unnamed: J14.1, U8.20 (GPIO12/TOUCH12/ADC2_CH1/FSPICLK/FSPIIO6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)
unnamed: J15.1, U8.21 (GPIO13/TOUCH13/ADC2_CH2/FSPIQ/FSPIIO7/S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)
unnamed: J9.4, J18.R, R12.2
unnamed: J9.5, J18.T, R13.2
unnamed: C17.2, J19.1, U1.1, U1.2 (-)
unnamed: C18.2, J21.1, U1.6 (-), U1.7
unnamed: J22.1, U8.11 (GPIO18/U1RXD/ADC2_CH7/CLK_OUT3)
unnamed: J23.1, U8.10 (GPIO17/U1TXD/ADC2_CH6)
unnamed: J24.1, U8.28 (SPIIO6/GPIO35/FSPID/SUBSPID)
unnamed: R35.1, R36.1, SW1.2 (B)
unnamed: C16.1, R26.2, U1.3 (+)
unnamed: C19.1, R29.2, U1.5 (+)
unnamed: C8.1, R8.2, U3.3 (+)
unnamed: C7.1, RV5.1, U3.1, U3.2 (-)
unnamed: C10.1, R10.2, U3.5 (+)
unnamed: C9.1, RV5.4, U3.6 (-), U3.7
unnamed: R3.1, R4.1, R5.2, U4.8 (A+)
unnamed: C3.1, C4.1, R36.2, U4.9 (A-)
unnamed: C4.2, C5.1, R35.2, U4.6 (B-)
unnamed: C11.1, R11.2, SW4.2, U8.3 (EN)
unnamed: R2.2, SW2.1, U8.27 (GPIO0/BOOT)
unnamed: RV3.2, U8.17 (GPIO9/TOUCH9/ADC1_CH8/FSPIHD/SUBSPIHD)
unnamed: RV4.2, U8.18 (GPIO10/TOUCH10/ADC1_CH9/FSPICS0/FSPIIO4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)
unnamed: C22.2, R31.1, U9.3 (+)
unnamed: R38.1, R39.2, U9.2 (-)
unnamed: C26.2, R34.1, U9.5 (+)
unnamed: R41.1, R42.2, U9.6 (-)
PT_BCK: U5.1 (BCK), U8.25 (GPIO48/SPICLK_N/SUBSPICLK_N_DIFF)
PT_DIN: U5.3 (DIN), U8.23 (GPIO21)
PT_L: R7.1, U5.6 (LCH)
PT_R: R9.1, U5.8 (RCH)
PT_WS: U5.2 (WS), U8.24 (GPIO47/SPICLK_P/SUBSPICLK_P_DIFF)
REG_IN: C1.1, C15.2, C24.2, D4.1 (K), D5.1 (K), R32.1, R33.1, SW1.3 (C), U2.3 (VI), U4.3 (V+), U9.8 (V+)
R_TO_SP: C29.1, R4.2, R42.1, U9.7
USB_PWR: D4.2 (A), J17.1 (VBUS)

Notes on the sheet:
CV/PWM SMOOTHING
SPEAKER AMP
POWER INPUT
SCL
POT 1
SDA
DAC
2nd order lpf: fc=21.2k
POT 0
AUDIO AMP
DIP SWITCH
MIDI I/O

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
